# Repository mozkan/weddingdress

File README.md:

# WedfestDress

Datasheets are not checked into this repository. They can be found here:
https://www.dropbox.com/sh/xb0569z05b4rpry/AAB6PzJzVCwgI6VpaBfMWfP8a?dl=0

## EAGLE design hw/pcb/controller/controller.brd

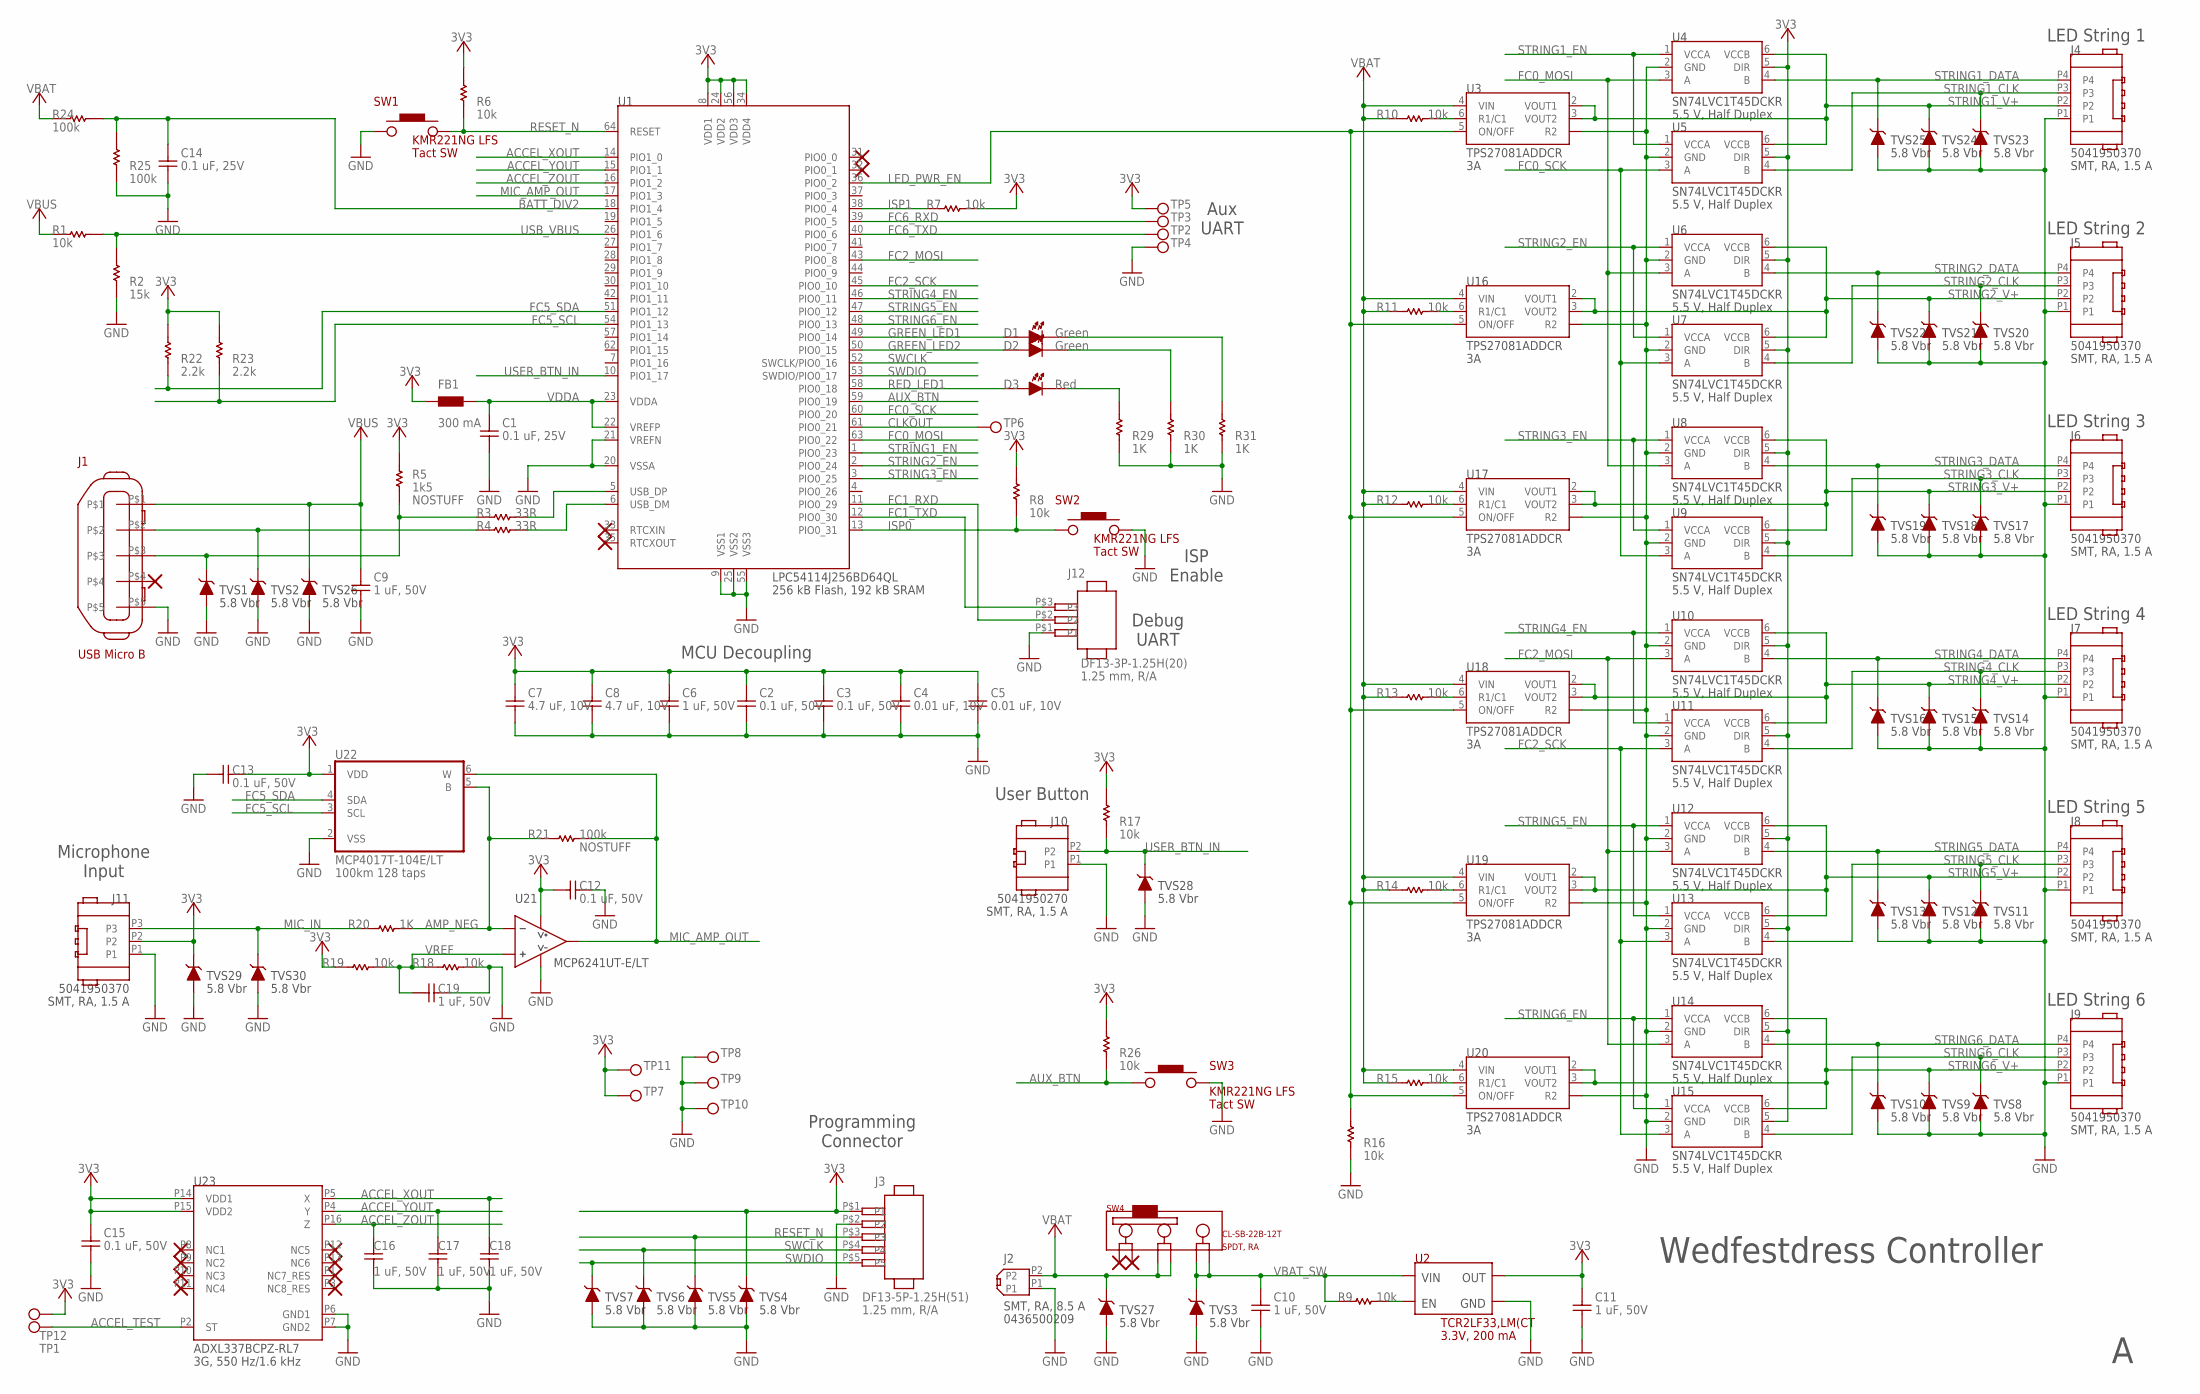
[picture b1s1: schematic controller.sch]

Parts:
C1, C14: CAP_GRM188R71E104KA01D; CAP_0603
C2, C3, C12, C13, C15: CAP_C1608X7R1H104K080AA; CAP_0603
C4, C5: CAP_CL10B103KB8NNNC; CAP_0603
C6, C9, C10, C11, C16, C17, C18, C19: CAP_GRM185R61C105KE44D; CAP_0603
C7, C8: CAP_CGB3B1X5R1A475M055AC; CAP_0603
D1, D2: LED_LTST-C190GKT; LED_0603
D3: LED_LS_Q976-NR-1; LED_0603_OSRAM
FB1: FB_BK1608TS102-T; FB_0603
J1: 10118192-0001LF
J2: MOLEX_0436500209; MOLEX_MICROFIT_2POS_SMT_RA_W_BOSSES
J3: DF13-5P-1.25H
J4, J5, J6, J7, J8, J9: MOLEX_5041950470; MOLEX_MICROLOCK_RA_4_POS
J10: MOLEX_5041950270; MOLEX_MICROLOCK_RA_2_POS
J11: MOLEX_5041950370; MOLEX_MICROLOCK_RA_3_POS
J12: DF13-3P-1.25H
R1, R6, R7, R8, R9, R10, R11, R12, R13, R14, R15, R16, R17, R18, R19, R26: RES_10K_RC0603FR-0710KL; RES_0603
R2: RES_15K_RC0603FR-0715KL; RES_0603
R3, R4: RES_33R_RC0603FR-0733RL; RES_0603
R5: RES_1K5_RC0603FR-071K5L; RES_0603
R20, R29, R30, R31: RES_1K_ERJ-3EKF1001V; RES_0603
R21, R24, R25: RES_100K_RC0603FR-07100KL; RES_0603
R22, R23: RES_2K2_ERJ-3EKF2201V; RES_0603
SW1, SW2, SW3: KMR221NG; KMR2
SW4: CL-SB-22B-12T
TP1, TP2, TP3, TP4, TP5, TP6, TP7, TP8, TP9, TP10, TP11, TP12: TP_1P6_MM_ROUND
TVS1, TVS2, TVS3, TVS4, TVS5, TVS6, TVS7, TVS8, TVS9, TVS10, TVS11, TVS12, TVS13, TVS14, TVS15, TVS16, TVS17, TVS18, TVS19, TVS20, TVS21, TVS22, TVS23, TVS24, TVS25, TVS26, TVS27, TVS28, TVS29, TVS30: PESD5V0X1UB,135; SOD523
U1: LPC54114J256BD64; LQFP64_0P5MM_10X10MM
U2: TCR2LF33,LM(CT; TOSHIBA_SMV
U3, U16, U17, U18, U19, U20: TPS27081; SOT-23-6_GENERIC
U4, U5, U6, U7, U8, U9, U10, U11, U12, U13, U14, U15: SN74LVC1T45DCKR; SC-70-6_GENERIC
U21: MCP6241UT-E/LT; SC-70-5_GENERIC
U22: MCP4017T; SOT65P210X110-6N
U23: ADXL337

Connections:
3V3: C2.P$1, C3.P$1, C4.P$1, C5.P$1, C6.P$1, C7.P$1, C8.P$1, C11.P$1, C12.P$1, C13.P$2, C15.P$1, FB1.P$1, J3.P$1 (P1), J11.P2, R5.P$2, R6.P$2, R7.P$1, R8.P$2, R17.P$2, R19.P$2, R22.P$2, R23.P$2, R26.P$2, TP5.P$1, TP7.P$1, TP11.P$1, TP12.P$1, TVS4.K, TVS29.K, U1.8 (VDD1), U1.24 (VDD2), U1.34 (VDD4), U1.56 (VDD3), U2.P5 (OUT), U4.5 (DIR), U5.5 (DIR), U6.5 (DIR), U7.5 (DIR), U8.5 (DIR), U9.5 (DIR), U10.5 (DIR), U11.5 (DIR), U12.5 (DIR), U13.5 (DIR), U14.5 (DIR), U15.5 (DIR), U21.5 (V+), U22.1 (VDD), U23.P14 (VDD1), U23.P15 (VDD2)
+6V: C9.P$1, J1.P$1, R1.P$2, TVS26.K
ACCEL_TEST: TP1.P$1, U23.P2 (ST)
ACCEL_XOUT: C18.P$1, U1.14 (PIO1_0), U23.P5 (X)
ACCEL_YOUT: C17.P$1, U1.15 (PIO1_1), U23.P4 (Y)
ACCEL_ZOUT: C16.P$1, U1.16 (PIO1_2), U23.P16 (Z)
AMP_NEG: R20.P$2, R21.P$1, U21.3 (IN-), U22.5 (B)
AUX_BTN: R26.P$1, SW3.P1, U1.59 (PIO0_19)
BATT_DIV2: C14.P$1, R24.P$1, R25.P$2, U1.18 (PIO1_4)
CLKOUT: TP6.P$1, U1.61 (PIO0_21)
FC0_MOSI: U1.63 (PIO0_22), U4.3 (A), U6.3 (A), U8.3 (A)
FC0_SCK: U1.60 (PIO0_20), U5.3 (A), U7.3 (A), U9.3 (A)
FC1_RXD: J12.P$2 (P2), U1.11 (PIO0_29)
FC1_TXD: J12.P$3 (P3), U1.12 (PIO0_30)
FC2_MOSI: U1.43 (PIO0_8), U10.3 (A), U12.3 (A), U14.3 (A)
FC2_SCK: U1.45 (PIO0_10), U11.3 (A), U13.3 (A), U15.3 (A)
FC5_SCL: R23.P$1, U1.54 (PIO1_13), U22.3 (SCL)
FC5_SDA: R22.P$1, U1.51 (PIO1_12), U22.4 (SDA)
FC6_RXD: TP3.P$1, U1.39 (PIO0_5)
FC6_TXD: TP2.P$1, U1.40 (PIO0_6)
GND: C1.P$2, C2.P$2, C3.P$2, C4.P$2, C5.P$2, C6.P$2, C7.P$2, C8.P$2, C9.P$2, C10.P$2, C11.P$2, C12.P$2, C13.P$1, C14.P$2, C15.P$2, C16.P$2, C17.P$2, C18.P$2, C19.P$2, J1.P$5, J2.P1, J3.P$2 (P2), J4.P1, J5.P1, J6.P1, J7.P1, J8.P1, J9.P1, J10.P1, J11.P1, J12.P$1 (P1), R2.P$1, R16.P$1, R18.P$1, R25.P$1, R29.P$1, R30.P$1, R31.P$1, SW1.P1, SW2.P3 (P2), SW3.P3 (P2), TP4.P$1, TP8.P$1, TP9.P$1, TP10.P$1, TVS1.A, TVS2.A, TVS3.A, TVS4.A, TVS5.A, TVS6.A, TVS7.A, TVS8.A, TVS9.A, TVS10.A, TVS11.A, TVS12.A, TVS13.A, TVS14.A, TVS15.A, TVS16.A, TVS17.A, TVS18.A, TVS19.A, TVS20.A, TVS21.A, TVS22.A, TVS23.A, TVS24.A, TVS25.A, TVS26.A, TVS27.A, TVS28.A, TVS29.A, TVS30.A, U1.9 (VSS1), U1.20 (VSSA), U1.21 (VREFN), U1.25 (VSS2), U1.55 (VSS3), U2.P2 (GND), U3.1 (R2), U4.2 (GND), U5.2 (GND), U6.2 (GND), U7.2 (GND), U8.2 (GND), U9.2 (GND), U10.2 (GND), U11.2 (GND), U12.2 (GND), U13.2 (GND), U14.2 (GND), U15.2 (GND), U16.1 (R2), U17.1 (R2), U18.1 (R2), U19.1 (R2), U20.1 (R2), U21.2 (V-), U22.2 (VSS), U23.P6 (GND1), U23.P7 (GND2)
GREEN_LED1: D1.A, U1.49 (PIO0_14)
GREEN_LED2: D2.A, U1.50 (PIO0_15)
ISP0: R8.P$1, SW2.P1, U1.13 (PIO0_31)
ISP1: R7.P$2, U1.38 (PIO0_4)
LED_PWR_EN: R16.P$2, U1.36 (PIO0_2), U3.5 (ON/OFF), U16.5 (ON/OFF), U17.5 (ON/OFF), U18.5 (ON/OFF), U19.5 (ON/OFF), U20.5 (ON/OFF)
MIC_AMP_OUT: R21.P$2, U1.17 (PIO1_3), U21.4 (OUT), U22.6 (W)
MIC_IN: J11.P3, R20.P$1, TVS30.K
unnamed: R10.P$2, U3.6 (R1/C1)
unnamed: R3.P$2, U1.5 (USB_DP)
unnamed: R4.P$2, U1.6 (USB_DM)
unnamed: J1.P$2, R4.P$1, TVS2.K
unnamed: J1.P$3, R3.P$1, R5.P$1, TVS1.K
unnamed: R9.P$1, U2.P3 (EN)
unnamed: D3.K, R29.P$2
unnamed: D2.K, R30.P$2
unnamed: D1.K, R31.P$2
unnamed: R15.P$2, U20.6 (R1/C1)
unnamed: R11.P$2, U16.6 (R1/C1)
unnamed: R12.P$2, U17.6 (R1/C1)
unnamed: R13.P$2, U18.6 (R1/C1)
unnamed: R14.P$2, U19.6 (R1/C1)
RED_LED1: D3.A, U1.58 (PIO0_18)
RESET_N: J3.P$3 (P3), R6.P$1, SW1.P3 (P2), TVS5.K, U1.64 (RESET)
STRING1_CLK: J4.P3, TVS23.K, U5.4 (B)
STRING1_DATA: J4.P4, TVS25.K, U4.4 (B)
STRING1_EN: U1.1 (PIO0_23), U4.1 (VCCA), U5.1 (VCCA)
STRING1_V+: J4.P2, TVS24.K, U3.2 (VOUT1), U3.3 (VOUT2), U4.6 (VCCB), U5.6 (VCCB)
STRING2_CLK: J5.P3, TVS20.K, U7.4 (B)
STRING2_DATA: J5.P4, TVS22.K, U6.4 (B)
STRING2_EN: U1.2 (PIO0_24), U6.1 (VCCA), U7.1 (VCCA)
STRING2_V+: J5.P2, TVS21.K, U6.6 (VCCB), U7.6 (VCCB), U16.2 (VOUT1), U16.3 (VOUT2)
STRING3_CLK: J6.P3, TVS17.K, U9.4 (B)
STRING3_DATA: J6.P4, TVS19.K, U8.4 (B)
STRING3_EN: U1.3 (PIO0_25), U8.1 (VCCA), U9.1 (VCCA)
STRING3_V+: J6.P2, TVS18.K, U8.6 (VCCB), U9.6 (VCCB), U17.2 (VOUT1), U17.3 (VOUT2)
STRING4_CLK: J7.P3, TVS14.K, U11.4 (B)
STRING4_DATA: J7.P4, TVS16.K, U10.4 (B)
STRING4_EN: U1.46 (PIO0_11), U10.1 (VCCA), U11.1 (VCCA)
STRING4_V+: J7.P2, TVS15.K, U10.6 (VCCB), U11.6 (VCCB), U18.2 (VOUT1), U18.3 (VOUT2)
STRING5_CLK: J8.P3, TVS11.K, U13.4 (B)
STRING5_DATA: J8.P4, TVS13.K, U12.4 (B)
STRING5_EN: U1.47 (PIO0_12), U12.1 (VCCA), U13.1 (VCCA)
STRING5_V+: J8.P2, TVS12.K, U12.6 (VCCB), U13.6 (VCCB), U19.2 (VOUT1), U19.3 (VOUT2)
STRING6_CLK: J9.P3, TVS8.K, U15.4 (B)
STRING6_DATA: J9.P4, TVS10.K, U14.4 (B)
STRING6_EN: U1.48 (PIO0_13), U14.1 (VCCA), U15.1 (VCCA)
STRING6_V+: J9.P2, TVS9.K, U14.6 (VCCB), U15.6 (VCCB), U20.2 (VOUT1), U20.3 (VOUT2)
SWCLK: J3.P$4 (P4), TVS6.K, U1.52 (SWCLK/PIO0_16)
SWDIO: J3.P$5 (P5), TVS7.K, U1.53 (SWDIO/PIO0_17)
USB_VBUS: R1.P$1, R2.P$2, U1.26 (PIO1_6)
USER_BTN_IN: J10.P2, R17.P$1, TVS28.K, U1.10 (PIO1_17)
VBAT: J2.P2, R10.P$1, R11.P$1, R12.P$1, R13.P$1, R14.P$1, R15.P$1, R24.P$2, SW4.3, SW4.4, TVS27.K, U3.4 (VIN), U16.4 (VIN), U17.4 (VIN), U18.4 (VIN), U19.4 (VIN), U20.4 (VIN)
VBAT_SW: C10.P$1, R9.P$2, SW4.5, SW4.6, TVS3.K, U2.P1 (VIN)
VDDA: C1.P$1, FB1.P$2, U1.22 (VREFP), U1.23 (VDDA)
VREF: C19.P$1, R18.P$2, R19.P$1, U21.1 (IN+)

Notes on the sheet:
Wedfestdress Controller
Programming Connector
MCU Decoupling
LED String 1
LED String 2
LED String 3
LED String 4
LED String 5
LED String 6
Debug UART
ISP Enable
User Button
Microphone Input
Aux UART

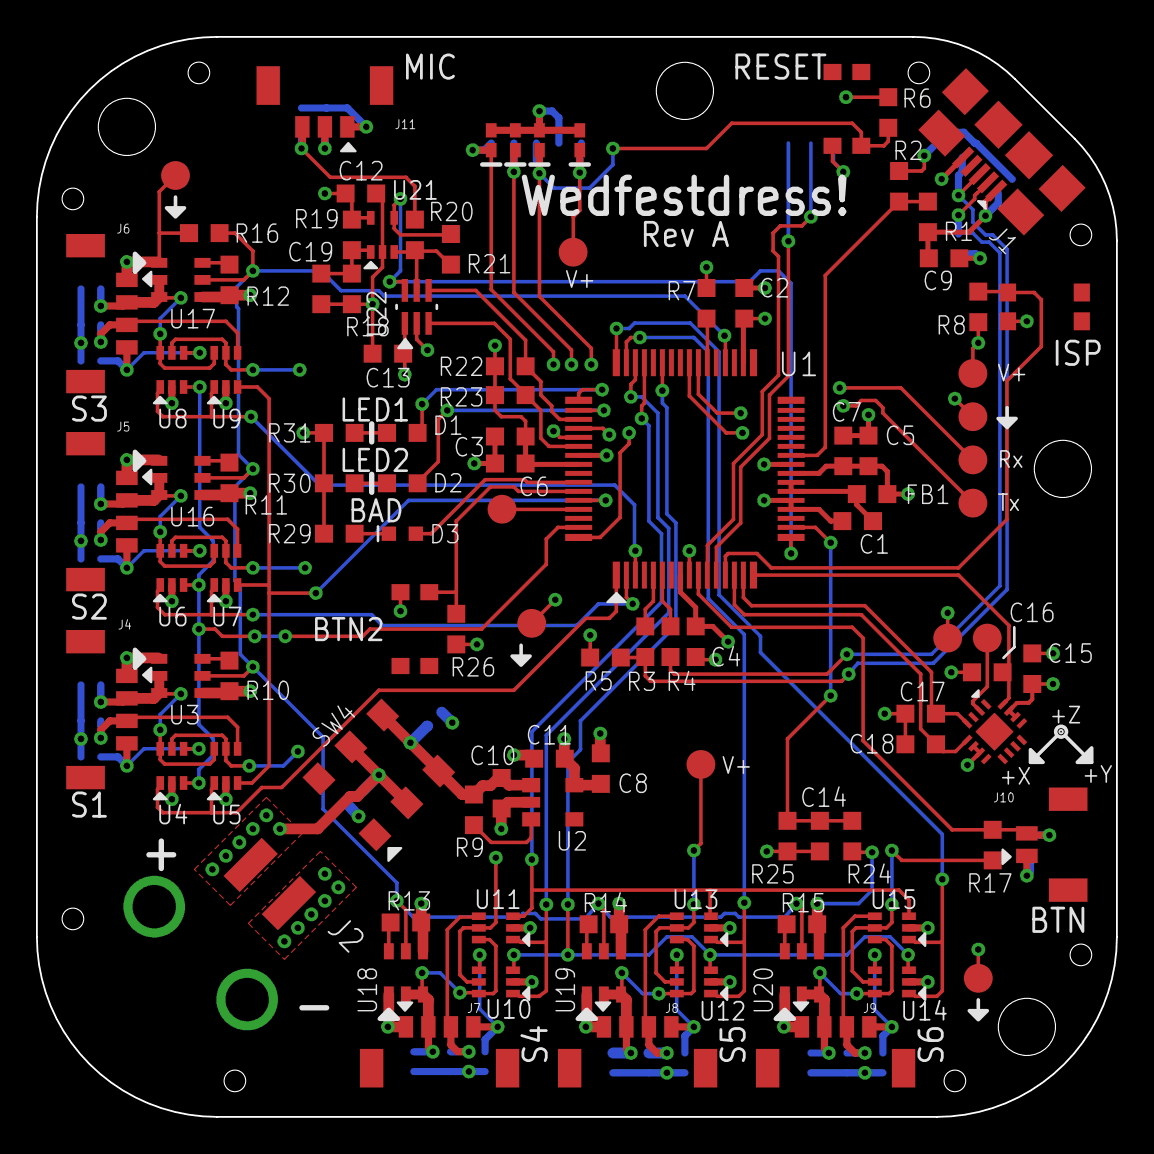
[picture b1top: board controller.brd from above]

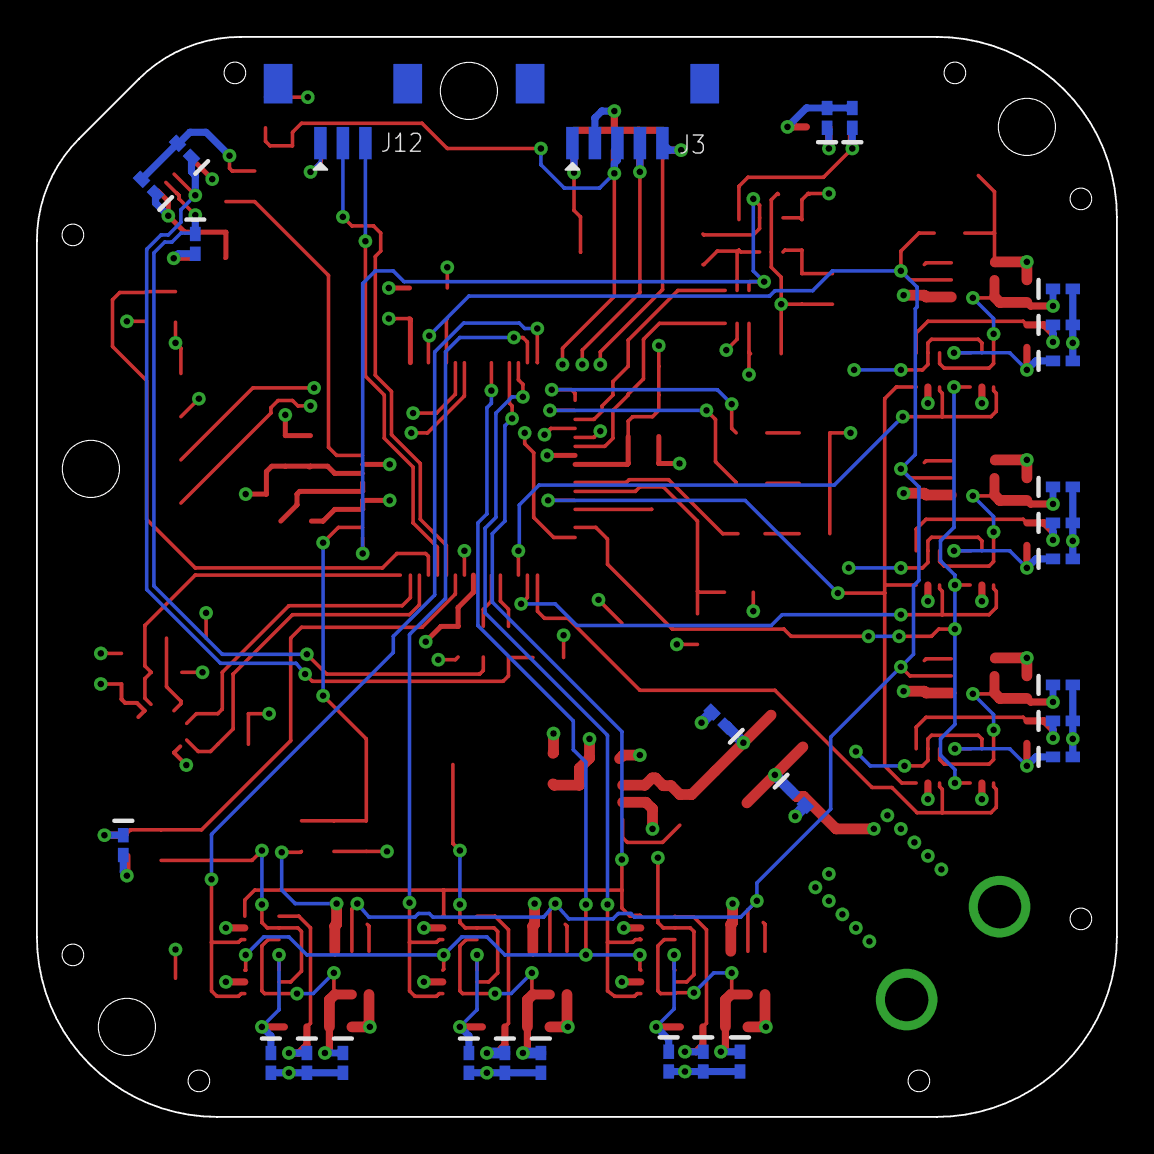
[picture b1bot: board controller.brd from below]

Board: 4 copper layers, 60.0 x 60.0 mm, 133 parts (28 on the bottom side), 76 nets.

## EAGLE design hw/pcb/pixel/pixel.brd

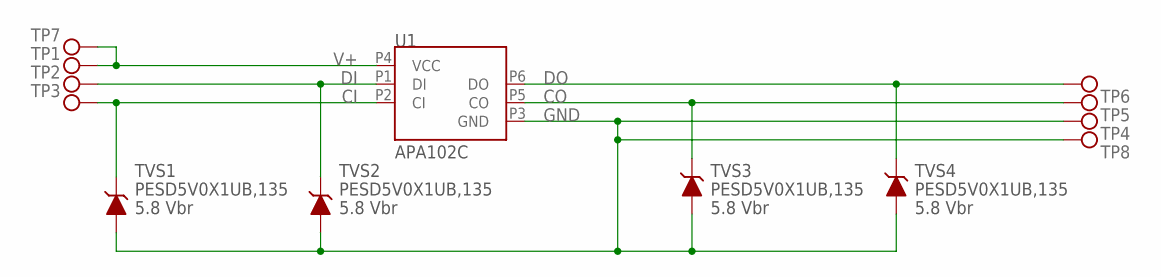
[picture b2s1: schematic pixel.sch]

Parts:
TP1, TP2, TP3, TP4, TP5, TP6, TP7, TP8: TP_1P6_MM_ROUND
TVS1, TVS2, TVS3, TVS4: PESD5V0X1UB,135; SOD523
U1: APA102C

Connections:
CI: TP3.P$1, TVS1.K, U1.P2 (CI)
CO: TP5.P$1, TVS3.K, U1.P5 (CO)
DI: TP2.P$1, TVS2.K, U1.P1 (DI)
DO: TP6.P$1, TVS4.K, U1.P6 (DO)
GND: TP4.P$1, TP8.P$1, TVS1.A, TVS2.A, TVS3.A, TVS4.A, U1.P3 (GND)
V+: TP1.P$1, TP7.P$1, U1.P4 (VCC)

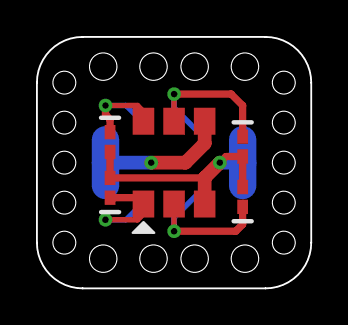
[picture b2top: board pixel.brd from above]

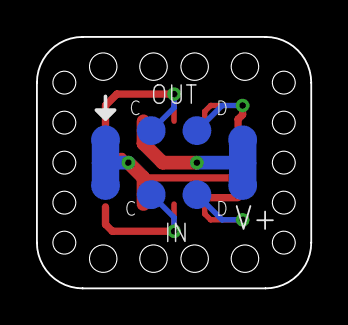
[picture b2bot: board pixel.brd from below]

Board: 2 copper layers, 15.2 x 14.0 mm, 13 parts (8 on the bottom side), 6 nets.

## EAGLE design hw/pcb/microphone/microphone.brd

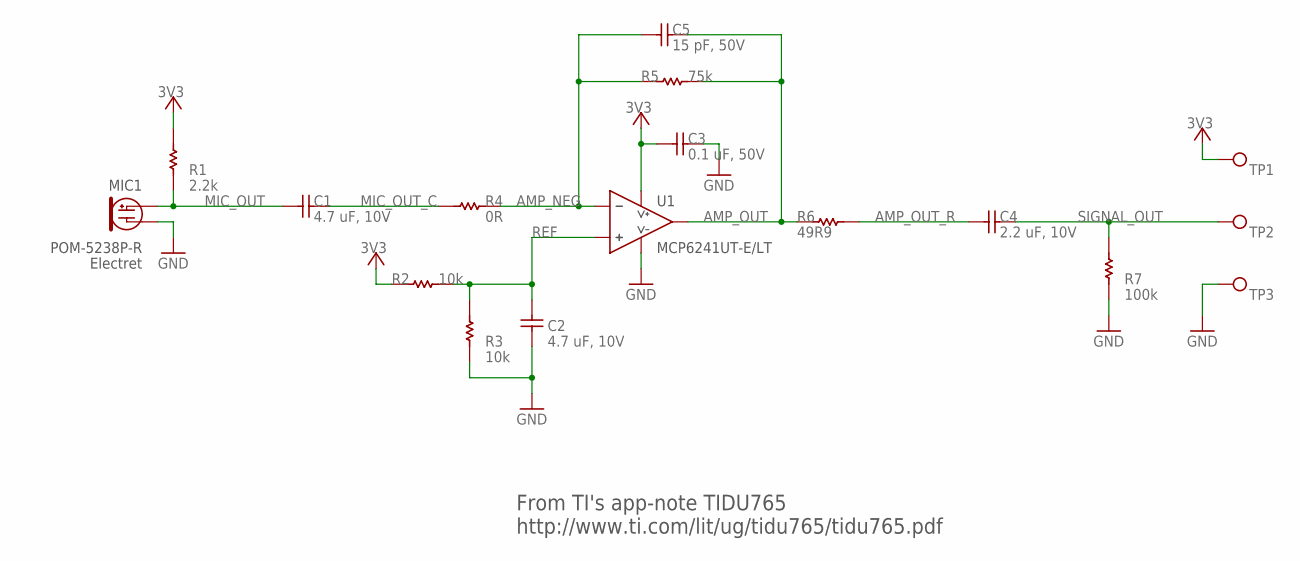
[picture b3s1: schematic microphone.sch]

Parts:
C1, C2: CAP_CGB3B1X5R1A475M055AC; CAP_0603
C3: CAP_C1608X7R1H104K080AA; CAP_0603
C4: CAP_CL10A225KP8NNNC; CAP_0603
C5: CAP_CL10C150JB8NNNC; CAP_0603
MIC1: POM-5238P-R
R1: RES_2K2_ERJ-3EKF2201V; RES_0603
R2, R3: RES_10K_RC0603FR-0710KL; RES_0603
R4: RES_0R_RC0603JR-070RL; RES_0603
R5: RES_75K_RC0603FR-0775KL; RES_0603
R6: RES_49R9_RC0603FR-0749R9L; RES_0603
R7: RES_100K_RC0603FR-07100KL; RES_0603
TP1, TP2, TP3: TP_1P6_MM_ROUND
U1: MCP6241UT-E/LT; SC-70-5_GENERIC

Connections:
3V3: C3.P$1, R1.P$2, R2.P$2, TP1.P$1, U1.5 (V+)
AMP_NEG: C5.P$1, R4.P$2, R5.P$1, U1.3 (IN-)
AMP_OUT: C5.P$2, R5.P$2, R6.P$1, U1.4 (OUT)
AMP_OUT_R: C4.P$1, R6.P$2
GND: C2.P$1, C3.P$2, MIC1.NEG, R3.P$1, R7.P$1, TP3.P$1, U1.2 (V-)
MIC_OUT: C1.P$1, MIC1.POS, R1.P$1
MIC_OUT_C: C1.P$2, R4.P$1
REF: C2.P$2, R2.P$1, R3.P$2, U1.1 (IN+)
SIGNAL_OUT: C4.P$2, R7.P$2, TP2.P$1

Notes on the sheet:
From TI's app-note TIDU765 http://www.ti.com/lit/ug/tidu765/tidu765.pdf

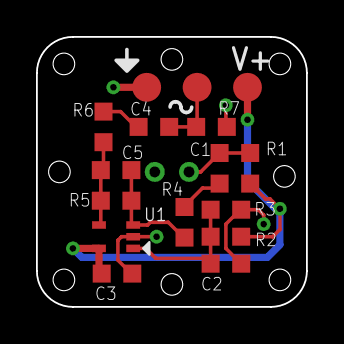
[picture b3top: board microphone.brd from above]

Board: 2 copper layers, 15.0 x 15.0 mm, 17 parts (1 on the bottom side), 9 nets.

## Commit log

2017-02-05 Initial set of calculations for wiring and power
    Sketched out some rough numbers for power consumption, battery life,
    wire gauge, LED spacing, etc. Good first pass for now.
2017-02-05 Update with link to datasheets on Dropbox
2017-02-05 Update project name
    Working title?
2017-02-05 Add blank set of Eagle design files
    Modified with LGPL license in XML. Files are blank with default
    schematic and layout settings.
2017-02-05 Add modified version of SFE CAM processor script
    Add a slightly modified version of the Sparkfun Eagle CAM processor
    script.
2017-02-09 First pass at pixel PCB
    - Add some library footprints.
    - First pass on schematic and layout of pixel PCB.
2017-02-10 Tweak hole placement and size, tweak design rules
    - Added holes for threading power wires twice instead of once.
    - Came up with a way to thread the signal wires into the power wired
    so that all are strain relieved well. Two holes on the threading
    holes (small) will be used to thread 28 AWG signal wires through.
    Signal wires will thread through the loop created by the power
    wires.
2017-06-12 Add gitignore
2017-06-12 Add CAM files for first rev of pixel pcb
2017-06-12 Update gitignore
    Ignore fab files. Use releases to track these packages.
2017-06-12 Draft of schematic is complete
    Still needs review.
2017-06-18 Routing and silscreen cleanup complete
2017-06-19 Add microphone board
    Completed schematic and layout of microphone board. Is a similar
    design to the one from TI's tidu765 app-note. Has provisions for a
    more basic non-inverting amplifier design as well. Currently uses a
    transimpedence amplifier.
2017-06-20 Add scripts
    - Added CAM generation script for 4 layer board based on Sparkfun's
    script.
    - Added helper script to copy CAM files generated by Eagle into the
    CAM directory.
    - Tweaks to microphone schematic (cosmetic).
2017-06-20 Final tweaks and CAM output for all three boards
2017-06-21 Prepare BOMs for purchasing
    Add BOM directories containing purchasing BOMs for the build.
    Sourced an alternate to the TVS to save some cost in case I need to
    buy 700 for the LEDs.
2017-06-25 Add purchasing BOMs for this build
    For Rev A of controller and microphone. Rev B of pixel board.
2017-07-05 Add initial source files for software
    Working through porting peripheral and board management management
    code from one of my other projects. Working through the MCU layer at
    the moment - lots of #if 0's still.
    Working in an MCUXpresso project for the time being to speed up setup
    time. Will eventually moved to a managed build, load, debug centered
    around bazel / GDB. Set up LPCOpen as its own static library with its
2017-07-21 Got SPI working on both ports
    Set up pin muxing, peripheral power, and peripheral configuration via
    wrapper class, SPIMaster. Level shifters also work.
    The method used to write to SPI is the simplest: polled + FIFO. Based
    on the activity observed on the scope there is quite a bit of
    overhead using the polled method - around 50%. Eventually, to improve
    processing bandwidth, DMA should be implemented.
2017-07-23 Display driver is written and tested in debugger
    Display driver is written and tested using oscilloscope. Proper write
    sequence and bit ordering looks right. Got a set of APA102 adhesive
    strips on a cardboard panel to test with. Almost ready to test with
    the real LEDs.
    Turned compiler optimizations on.
2017-07-26 Button read code compiles
    Have not tested. Need to implement timer code too.
2017-07-26 Display driver now tested to work
    Tested the display driver with real LEDs. SPI settings and APA102
    protocol implementation has now been verified. Single string update
    mode still has a bug in it. Not going to fix this right now.
2017-07-31 Add gamma correction to pixels
    Added gamma correction for pixel setters. Looks better now on linear
    brightness sweep test.
2017-07-31 Add timer functionality
    Got the timer peripheral working and integrated it into a basic HAL
    wrapper.
2017-08-01 Add pattern definition mechanism
    Added a pattern definition mechanism that consolidates the resource
    allocation into a parent class, and leaves only the pattern
    calculation to children.
2017-08-01 Add task management code with first pattern
    Add task management code to manage timing of arbitrary tasks to be run
    in a round-robin outer-most control loop (polymorphic). Integrate
    the first tested (demo) pattern into this as a pattern to be run
    within a "pattern runner" task. Other tasks will be created for
    checking the battery and polling the user button, for example.
2017-08-02 Wrote first pattern
    Wrote the actual AlternateRampPattern pattern. It's really bright...
2017-08-03 Add FlashyDinglerPattern
    WIP - Add a new pattern.
2017-08-04 Integrate button into Wedfestdress
    Add button polling into ButtonPollingTask task. Crude shared memory
    based inter task communication for now. Tomorrow is the wedding. Will
    replace with callback mechanism later. Callback mechanism seems the way
    to go.
    Pattern switching now works as well via button presses.
2017-08-04 Tweaks to FlashyDingler pattern, pattern runner
    Updated timing of FlashyDingler and changed its twinkle algorithm to
    have a moving midpoint from which to set the bounds to on the next
    ramp up/down. Also have the pattern runner reset the patterns when
    switching to a new one.
2017-08-10 Final tweaks before the wedding!
    Added an all dark pattern so that we can always start from a known
    state. On the dress, unlike on the tester platform, some pixels start
    stuck on. It was helpful to start it, get past this uninitialized
    state by getting back to the dark pattern, then doing the ramp to
    white when we kiss at the ceremony.
